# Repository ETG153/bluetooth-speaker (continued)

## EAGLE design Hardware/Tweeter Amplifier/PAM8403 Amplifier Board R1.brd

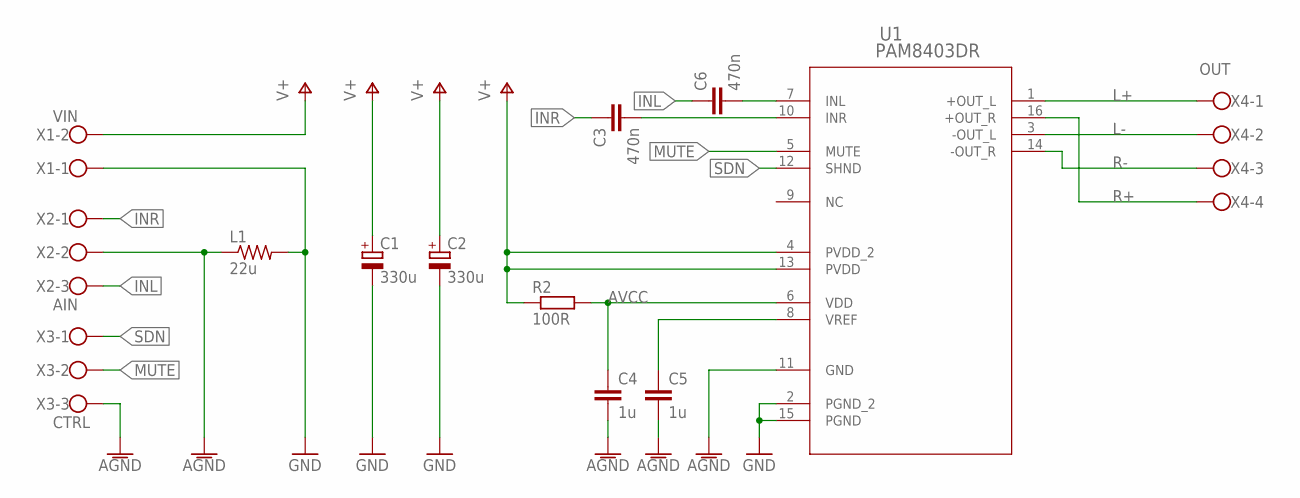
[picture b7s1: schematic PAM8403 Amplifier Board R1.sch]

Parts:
C1, C2: 330u; E3,5-8
C3, C6: 470n; C1206
C4, C5: 1u; C1206
L1: 22u; R0805
R2: 100R; R0603
U1: PAM8403DR; SOIC_8403DR_DIO
X1: VIN; W237-102
X2: AIN; W237-103
X3: CTRL; W237-103
X4: OUT; W237-4

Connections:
AGND: C4.2, C5.2, L1.1, U1.11 (GND), X2.2, X3.3
AVCC: C4.1, R2.2, U1.6 (VDD)
GND: C1.-, C2.-, L1.2, U1.2 (PGND_2), U1.15 (PGND), X1.1
INL: C6.1, X2.3
INR: C3.1, X2.1
L+: U1.1 (+OUT_L), X4.1
L-: U1.3 (-OUT_L), X4.2
MUTE: U1.5 (MUTE), X3.2
unnamed: C3.2, U1.10 (INR)
unnamed: C6.2, U1.7 (INL)
unnamed: C5.1, U1.8 (VREF)
R+: U1.16 (+OUT_R), X4.4
R-: U1.14 (-OUT_R), X4.3
SDN: U1.12 (SHND), X3.1
V+: C1.+, C2.+, R2.1, U1.4 (PVDD_2), U1.13 (PVDD), X1.2

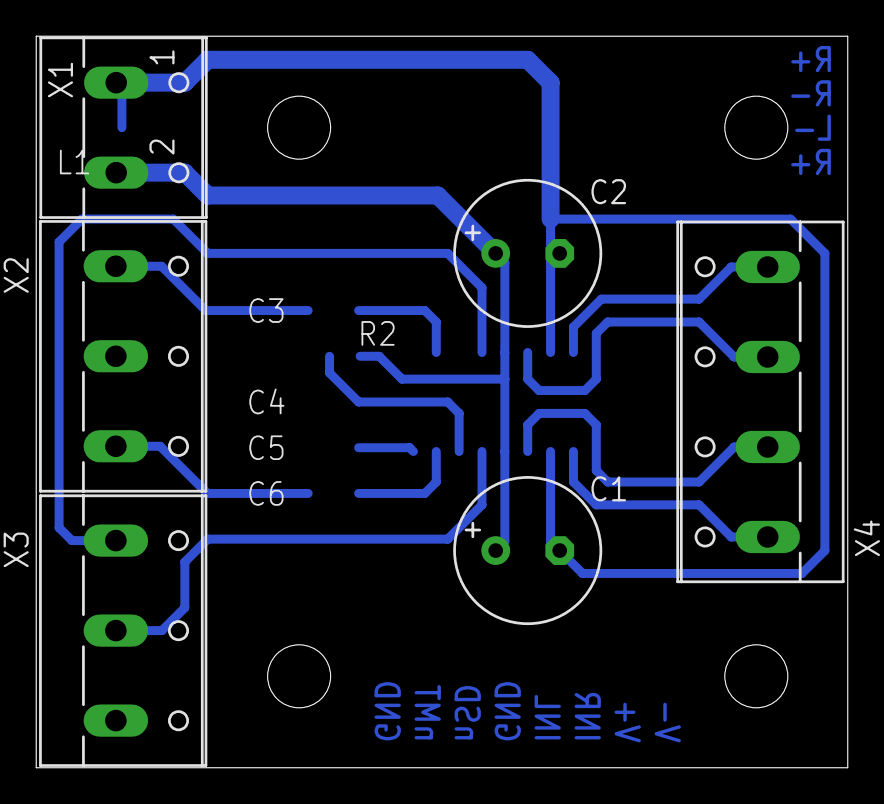
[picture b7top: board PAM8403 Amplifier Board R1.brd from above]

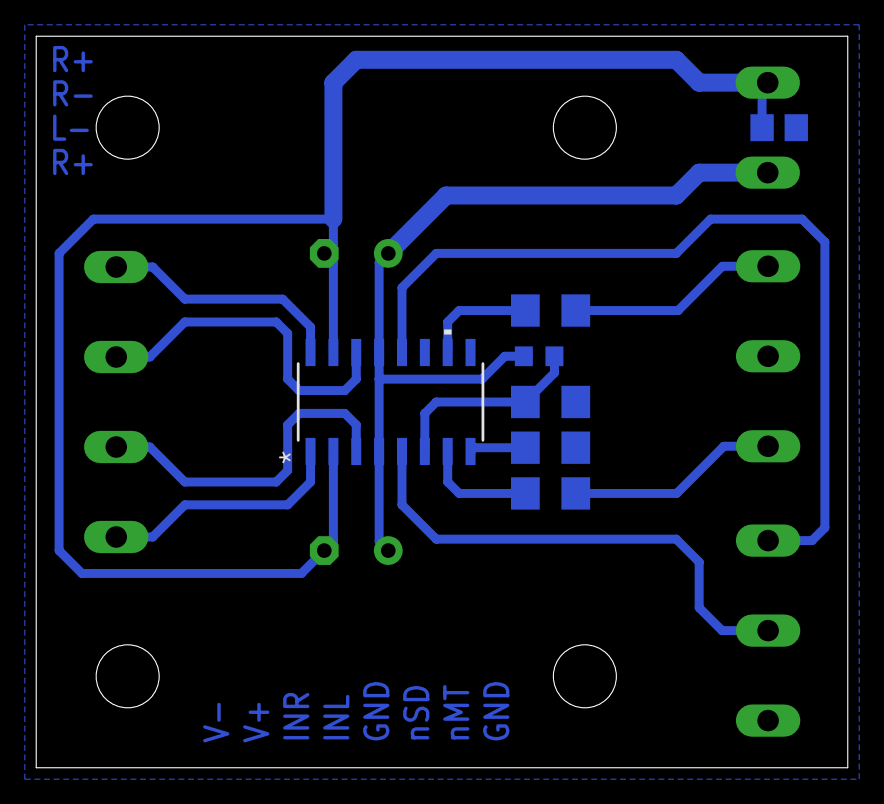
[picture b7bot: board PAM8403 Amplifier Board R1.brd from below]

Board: 2 copper layers, 45.1 x 40.6 mm, 13 parts (7 on the bottom side), 15 nets.
